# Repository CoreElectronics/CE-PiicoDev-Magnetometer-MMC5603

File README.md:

# PiicoDev® Magnetometer MMC5603

This is the repo for the Core Electronics [PiicoDev Magnetometer MMC5603](https://core-electronics.com.au/catalog/product/view/sku/CE10107).

The PiicoDev® Magnetometer measures invisible magnetic fields. It's sensitive enough to use as a compass and wide-range enough for detecting magnets - which have a much stronger field. The on-board MMC5603 can measure up to 20-bits up to 3000μT in all 3 axes. By using PiicoDev adapters and cables, you can connect to this sensor without soldering - or use the standard breakout header if you prefer breadboard prototyping. Whichever you prefer, the PiicoDev guides will guide you through exciting experiments like measuring the Earth's magnetic field to find a heading and detecting if a magnet is nearby.

**Features**

- Small size, high accuracy
- Measures magnetic fields in 3-axes
- Sensitive enough to use like a compass, 
- A broad enough range to work with nearby magnets
- Great guides to get you started
- PiicoDev connector, compatible with Qwiic and STEMMA QT (3.3V only)
- 2.54mm breakout for breadboarding/prototyping
- Manufactured and supported in Australia by Core Electronics

## License
This project is open source - please review the LICENSE.md file for further licensing information.

If you have any technical questions, or concerns about licensing, please contact technical support on the [Core Electronics forums](https://forum.core-electronics.com.au/).

*\"PiicoDev\" and the PiicoDev logo are trademarks of Core Electronics Pty Ltd.*

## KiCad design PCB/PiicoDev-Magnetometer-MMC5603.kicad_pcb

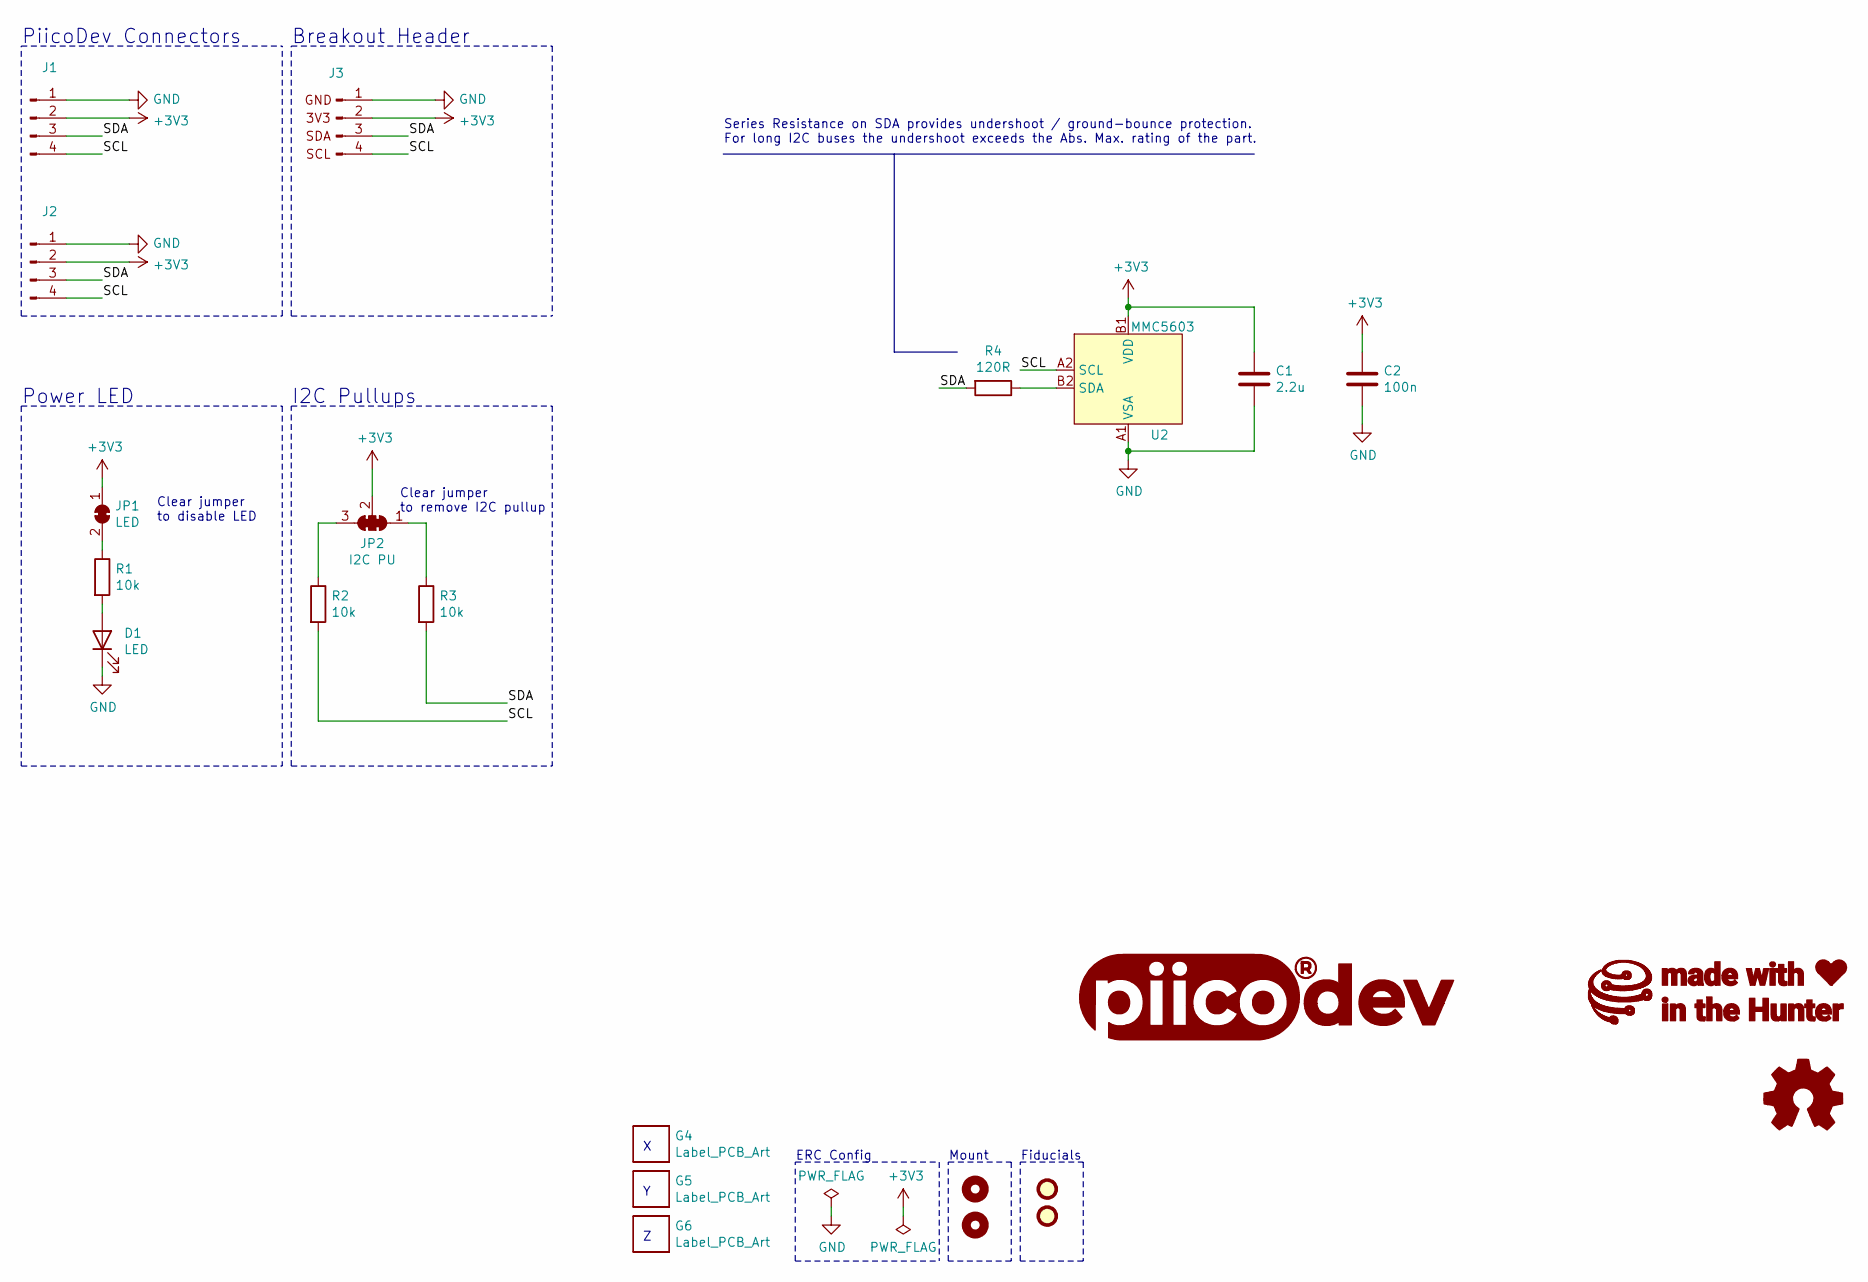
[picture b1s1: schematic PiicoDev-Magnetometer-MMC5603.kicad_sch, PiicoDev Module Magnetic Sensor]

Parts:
C1: 2.2u; C_0402_1005Metric
C2: 100n; C_0402_1005Metric
D1: LED; LED_0603_1608Metric
FID1, FID2: Fiducial; Fiducial_1mm_Mask2mm
G1: LOGO_PiicoDev; piicodev_logo_14.2x3.4mm
G2: LOGO_CoreElectronics_no-text; CoreElectronics_logo_5mm
G3: LOGO_made-with-love; piicodev_logo_14.2x3.4mm
G4: Label_PCB_Art; Axes_and_polarity_X
G5: Label_PCB_Art; Axes_and_polarity_Y
G6: Label_PCB_Art; Axes_and_polarity_Z
H1, H2: MountingHole; MountingHole_2.7mm_M2.5_PadClearance_1.2
J1, J2: JST_SH_SM04B-SRSS-TB_1x04-1MP_P1.00mm_Horizontal
J3: Conn_PiicoDev_header_01x04_Male; PiicoDev_header_4pin
JP1: LED; SolderJumper-2_P1.3mm_Bridged_RoundedPad1.0x1.5mm
JP2: I2C PU; SolderJumper-3_P1.3mm_Closed_RoundedPad1.0x1.5mm_NumberLabe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
LOGO1: Logo_Open_Hardware_Small; oshw
R1, R2, R3: 10k; R_0402_1005Metric
R4: 120R; R_0402_1005Metric
U2: MMC5603

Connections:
+3V3: C1.1, C2.1, J1.2, J2.2, J3.2, JP1.1 (A), JP2.2 (C), U2.B1 (VDD)
/SCL: J1.4, J2.4, J3.4, R2.2, U2.A2 (SCL)
/SDA: J1.3, J2.3, J3.3, R3.2, R4.2
GND: C1.2, C2.2, D1.1 (K), J1.1, J2.1, J3.1, U2.A1 (VSA)
unnamed: D1.2 (A), R1.2
unnamed: JP1.2 (B), R1.1
unnamed: JP2.1 (A), R3.1
unnamed: JP2.3 (B), R2.1
unnamed: R4.1, U2.B2 (SDA)

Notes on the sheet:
ERC Config
PiicoDev Connectors
Breakout Header
Mount
Fiducials
Series Resistance on SDA provides undershoot / ground-bounce protection. For long I2C buses the undershoot exceeds the Abs. Max. rating of the part.
Clear jumper to disable LED
Power LED
Clear jumper to remove I2C pullup
I2C Pullups

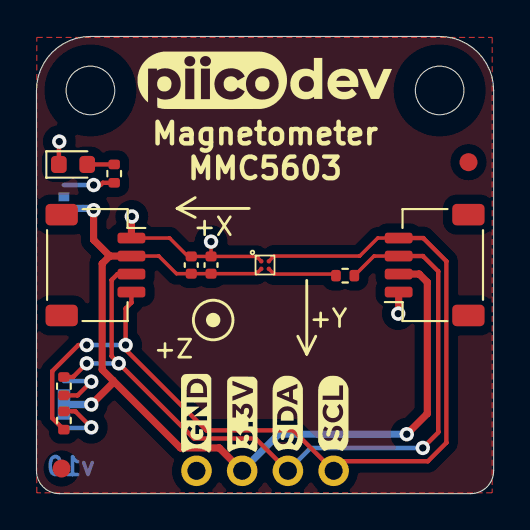
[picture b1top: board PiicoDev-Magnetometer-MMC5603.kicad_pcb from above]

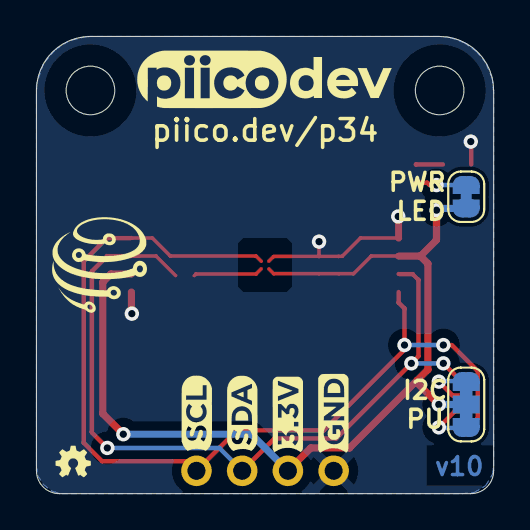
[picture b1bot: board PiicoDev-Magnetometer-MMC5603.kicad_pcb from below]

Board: 2 copper layers, 25.4 x 25.4 mm, 24 parts (6 on the bottom side), 9 nets.

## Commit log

2024-12-03 PCB complete, schematic and datasheet

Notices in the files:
PCB/PiicoDev-Magnetometer-MMC5603.kicad_sch:
License: CCASAv4.0 http://creativecommons.org/licenses/by-sa/4.0
